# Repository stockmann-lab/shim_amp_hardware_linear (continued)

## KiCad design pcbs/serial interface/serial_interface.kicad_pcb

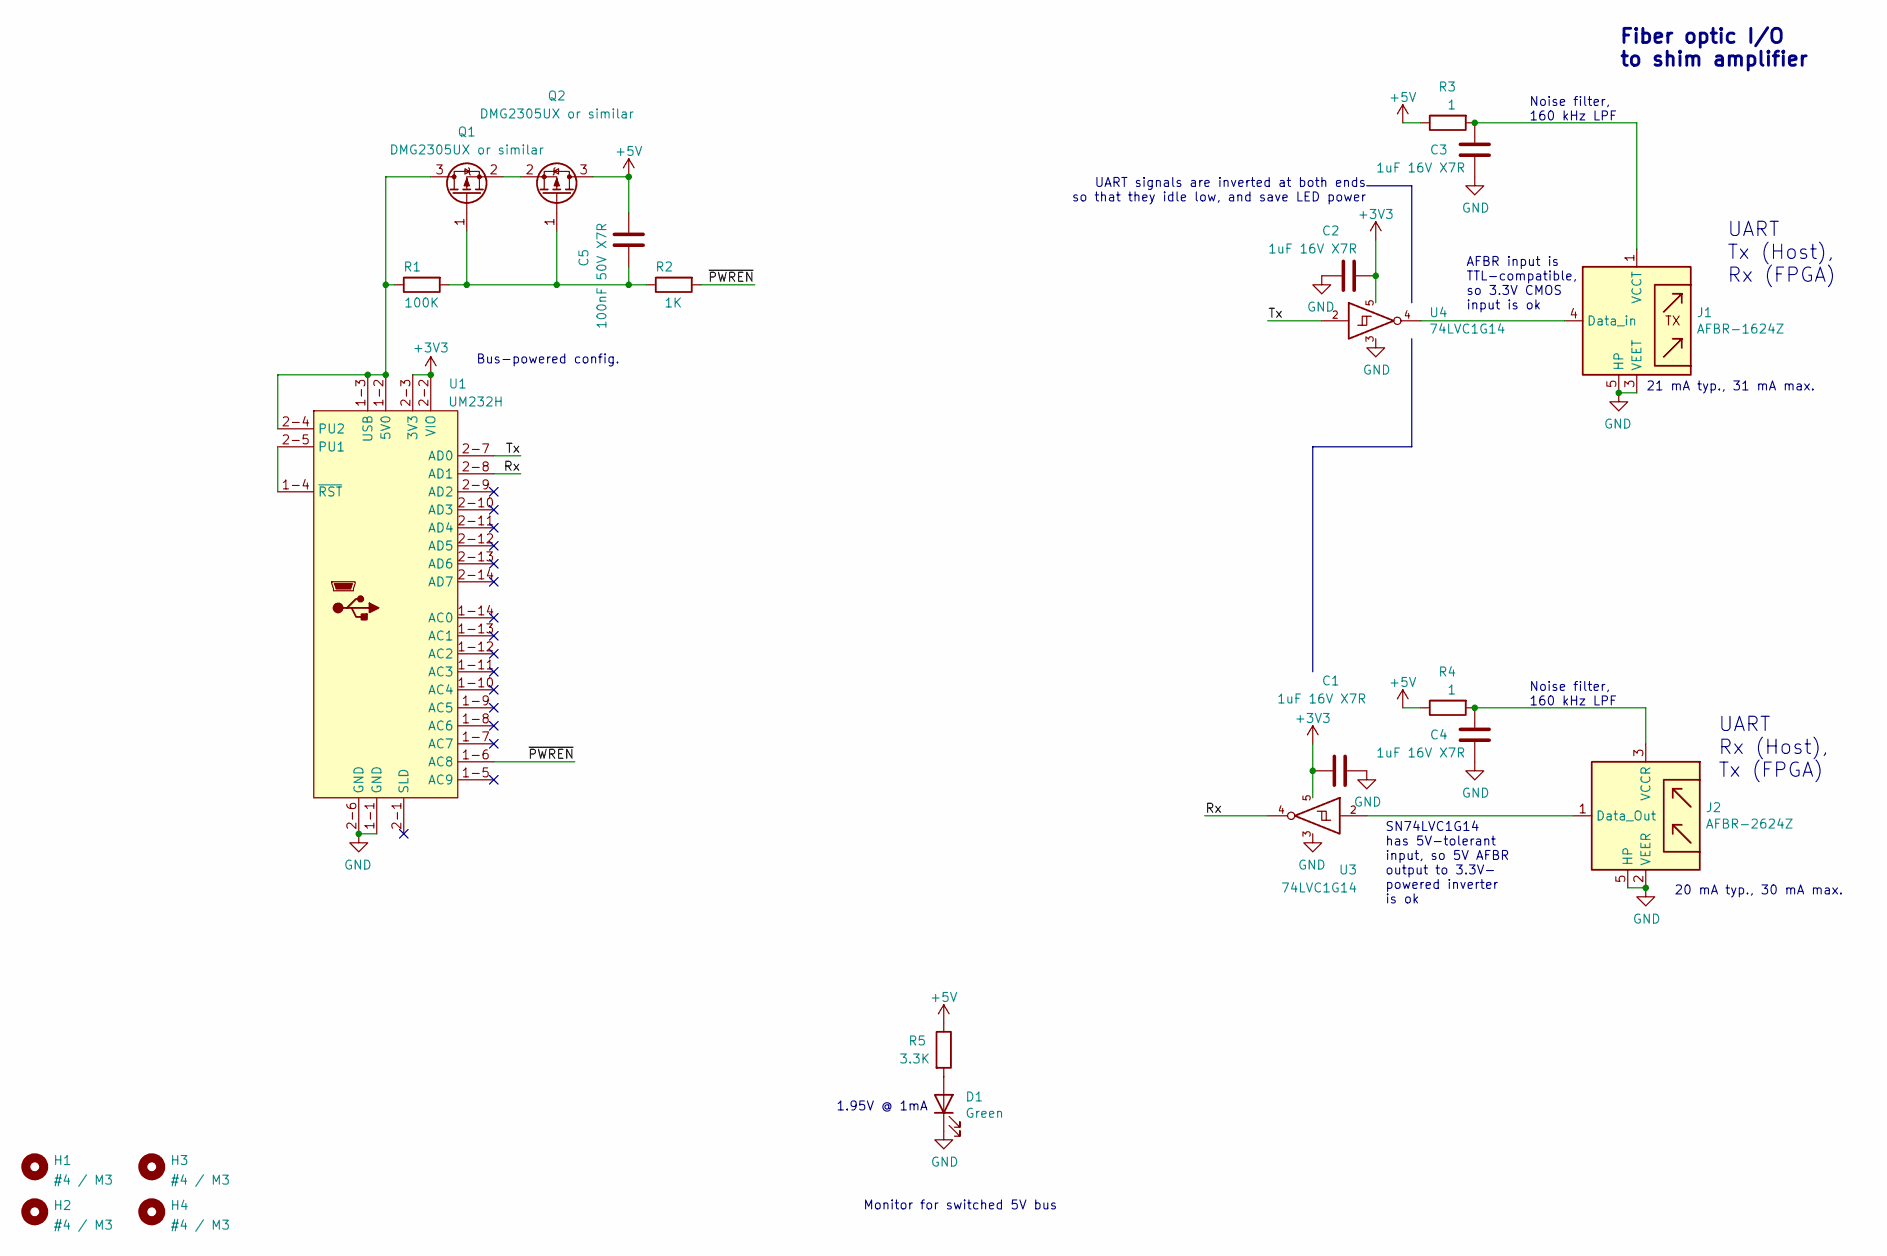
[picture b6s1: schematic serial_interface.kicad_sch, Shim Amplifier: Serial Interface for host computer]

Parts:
C1, C2, C3, C4: 1uF 16V X7R; C_0603_1608Metric; Part Number C0603C105K4RACTU
C5: 100nF 50V X7R; C_0603_1608Metric; Part Number C0603C104K5RAC7867
D1: Green; LED_0805_2012Metric; Part Number LTST-C171KGKT
H1, H2, H3, H4: #4 / M3; MountingHole_3.2mm_M3
J1: AFBR-1624Z; AFBR-xx2xZ; Part Number AFBR-1624Z
J2: AFBR-2624Z; AFBR-xx2xZ; Part Number AFBR-2624Z
Q1, Q2: DMG2305UX or similar; SOT-23
R1: 100K; R_0805_2012Metric
R2: 1K; R_0805_2012Metric
R3, R4: 1; R_0805_2012Metric; Part Number RK73H2ATTD1R00F
R5: 3.3K; R_0805_2012Metric; Part Number RK73H2ATTD1001F
U1: UM232H; FTDI_UM232H; Part Number UM232H
U3, U4: 74LVC1G14; SOT-23-5; Part Number SN74LVC1G14DBVR

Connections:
+3V3: C1.2, C2.2, U1.2-2 (VIO), U1.2-3 (3V3), U3.5 (VCC), U4.5 (VCC)
+5V: C5.2, Q2.3 (D), R3.1, R4.1, R5.1
/Rx: U1.2-8 (AD1), U3.4
/Tx: U1.2-7 (AD0), U4.2
/~PWREN: R2.2, U1.1-6 (AC8)
GND: C1.1, C2.1, C3.1, C4.1, D1.1 (K), J1.3 (VEET), J1.5 (HP), J1.8 (HP), J2.2 (VEER), J2.5 (HP), J2.8 (HP), U1.1-1 (GND), U1.2-6 (GND), U3.3 (GND), U4.3 (GND)
unnamed: D1.2 (A), R5.2
unnamed: J1.4 (Data_in), U4.4
unnamed: C3.2, J1.1 (VCCT), R3.2
unnamed: J2.1 (Data_Out), U3.2
unnamed: C4.2, J2.3 (VCCR), R4.2
unnamed: Q1.3 (D), R1.1, U1.1-2 (5V0), U1.1-3 (USB), U1.2-4 (PU2)
unnamed: C5.1, Q1.1 (G), Q2.1 (G), R1.2, R2.1
unnamed: Q1.2 (S), Q2.2 (S)
unnamed: U1.1-4 (~RST), U1.2-5 (PU1)

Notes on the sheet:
Noise filter, 160 kHz LPF
21 mA typ., 31 mA max.
AFBR input is TTL-compatible, so 3.3V CMOS input is ok
UART Rx (Host), Tx (FPGA)
UART Tx (Host), Rx (FPGA)
UART signals are inverted at both ends so that they idle low, and save LED power
Monitor for switched 5V bus
Bus-powered config.
1.95V @ 1mA
20 mA typ., 30 mA max.
Fiber optic I/O to shim amplifier
SN74LVC1G14 has 5V-tolerant input, so 5V AFBR output to 3.3V- powered inverter is ok

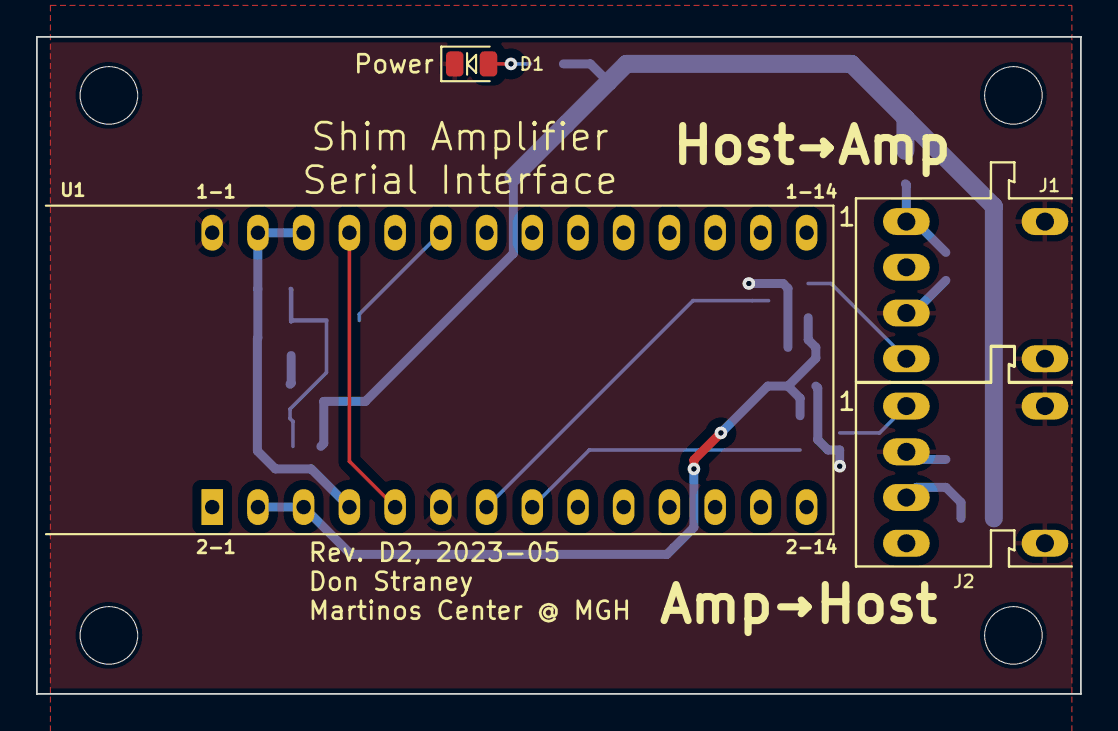
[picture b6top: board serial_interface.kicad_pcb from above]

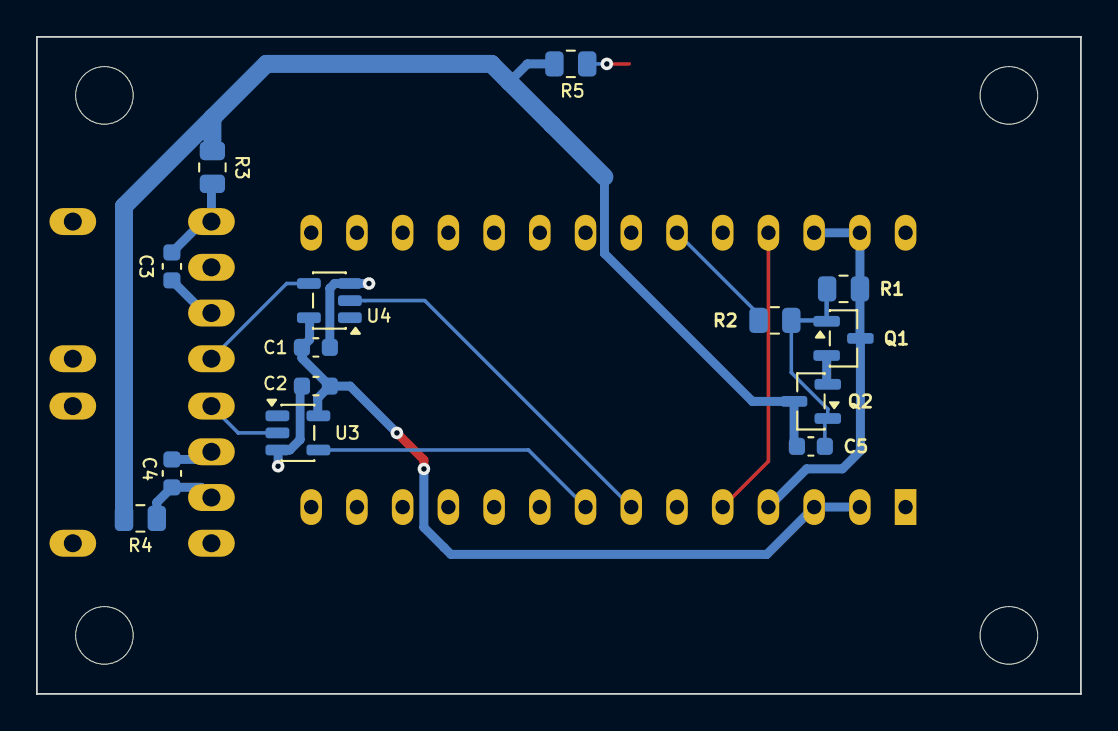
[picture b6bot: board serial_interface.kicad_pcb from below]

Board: 2 copper layers, 58.0 x 36.5 mm, 22 parts (14 on the bottom side), 15 nets.

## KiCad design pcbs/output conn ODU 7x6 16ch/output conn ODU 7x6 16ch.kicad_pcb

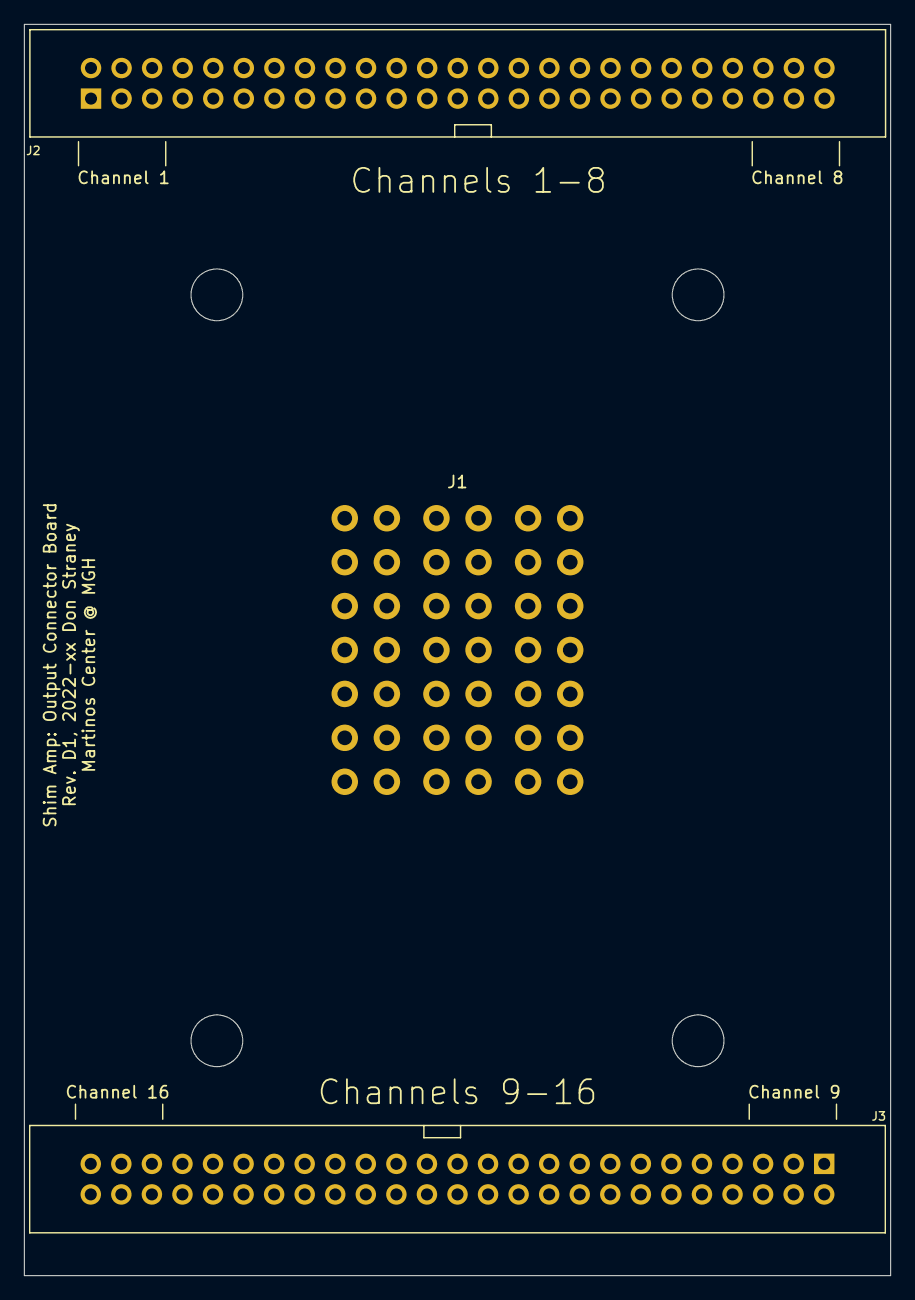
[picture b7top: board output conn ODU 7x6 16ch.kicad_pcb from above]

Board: 4 copper layers, 72.0 x 104.0 mm, 7 parts (1 on the bottom side), 32 nets, no tracks yet.

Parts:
H1, H2, H3, H4: M4; MountingHole_4.3mm_M4
J1: ODU-MAC_Zero_6x7
J2, J3: Conn_02x25_Odd_Even; PinHeader_2x25_P2.54mm_Vertical_Shrouded

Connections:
/P1+: J2.1, J2.3, J2.5
/P1-: J2.2, J2.4, J2.6
/P2+: J2.7, J2.9, J2.11
/P2-: J2.8, J2.10, J2.12
/P3+: J2.13, J2.15, J2.17
/P3-: J2.14, J2.16, J2.18
/P4+: J2.19, J2.21, J2.23
/P4-: J2.20, J2.22, J2.24
/P5+: J2.27, J2.29, J2.31
/P5-: J2.28, J2.30, J2.32
/P6+: J2.33, J2.35, J2.37
/P6-: J2.34, J2.36, J2.38
/P7+: J2.39, J2.41, J2.43
/P7-: J2.40, J2.42, J2.44
/P8+: J2.45, J2.47, J2.49
/P8-: J2.46, J2.48, J2.50
/P9+: J3.1, J3.3, J3.5
/P9-: J3.2, J3.4, J3.6
/P10+: J3.7, J3.9, J3.11
/P10-: J3.8, J3.10, J3.12
/P11+: J3.13, J3.15, J3.17
/P11-: J3.14, J3.16, J3.18
/P12+: J3.19, J3.21, J3.23
/P12-: J3.20, J3.22, J3.24
/P13+: J3.27, J3.29, J3.31
/P13-: J3.28, J3.30, J3.32
/P14+: J3.33, J3.35, J3.37
/P14-: J3.34, J3.36, J3.38
/P15+: J3.39, J3.41, J3.43
/P15-: J3.40, J3.42, J3.44
/P16+: J3.45, J3.47, J3.49
/P16-: J3.46, J3.48, J3.50

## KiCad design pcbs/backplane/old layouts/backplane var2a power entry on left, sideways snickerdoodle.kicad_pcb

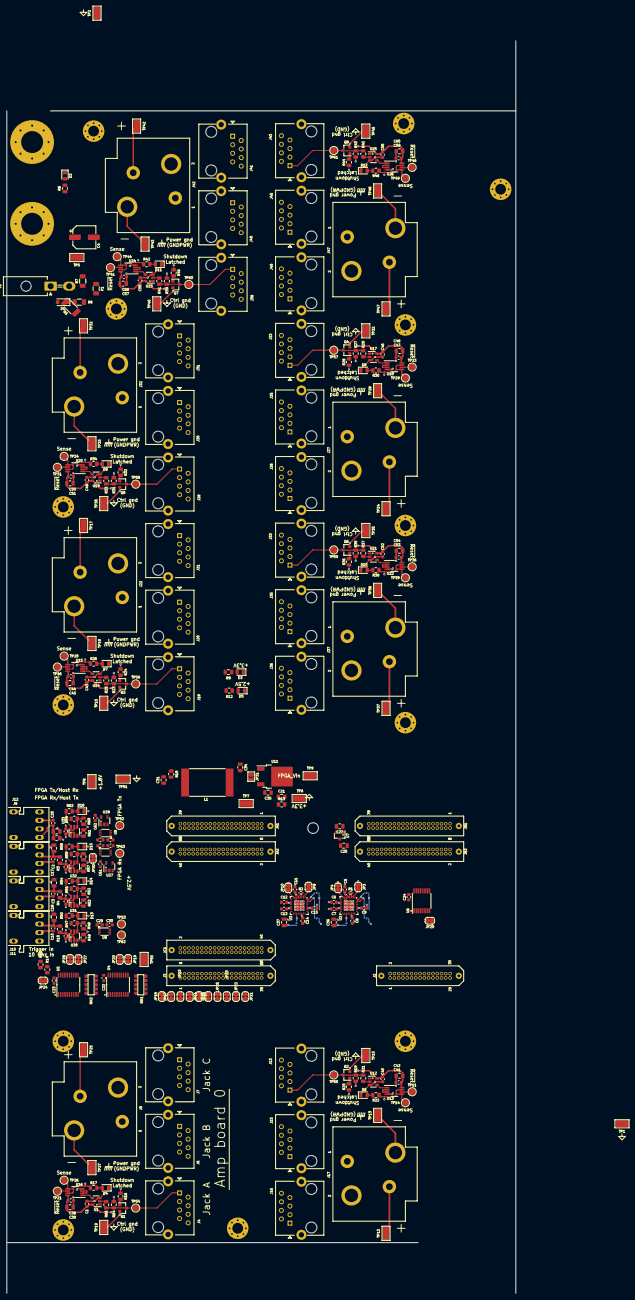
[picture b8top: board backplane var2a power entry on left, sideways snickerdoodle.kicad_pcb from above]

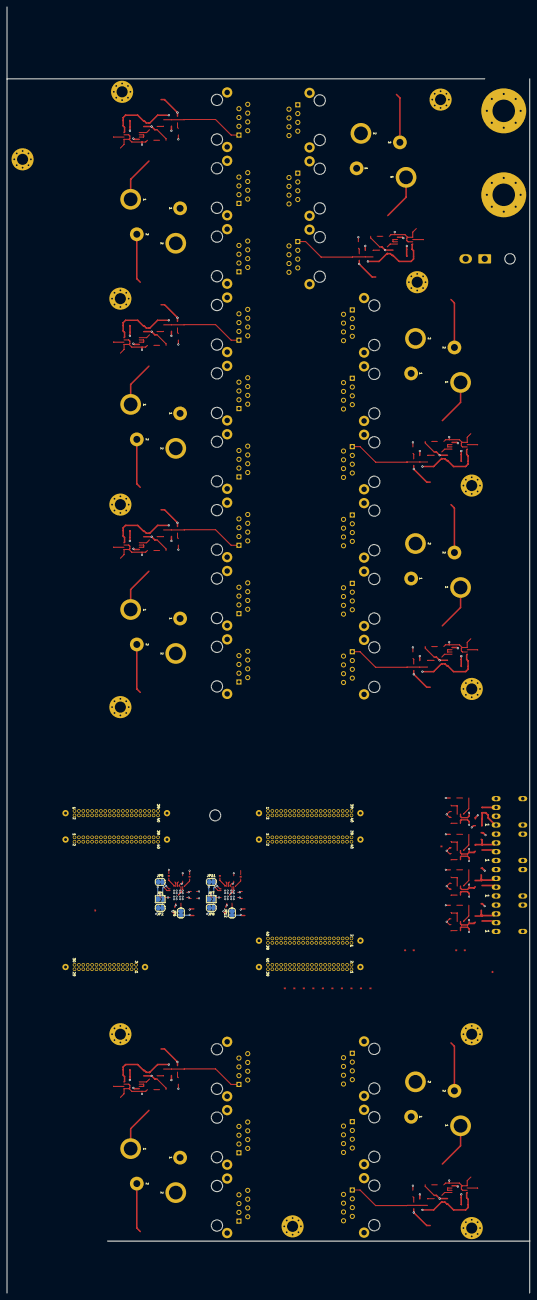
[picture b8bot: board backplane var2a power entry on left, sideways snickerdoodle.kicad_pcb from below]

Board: 6 copper layers, 151.0 x 371.5 mm, 341 parts (8 on the bottom side), 272 nets.

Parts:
C1, C2, C3, C5, C6, C7, C8, C9, C10, C11, C12, C13, C14, C15, C20, C22, C23, C24, C26, C28, C29, C30, C32, C33, C38, C40, C41, C43, C44, C46, C47, C49, C50, C52, C53, C55, C56, C58, C59, C61, C62, C63, C64, C65, C66: 100nF 50V X7R; C_0603_1608Metric
C4: 100uF 35V alum.; CP_Elec_6.3x9.9
C16, C17, C18, C19, C21, C25, C27, C31, C34, C35, C36, C37, C39, C42, C45, C48, C51, C54, C57, C60: 1uF 50V X7R; C_0805_2012Metric
D1: PMEG6010; D_SOD-123F
D2, D3, D5: Green; LED_0805_2012Metric
D4, D6, D7, D8, D9, D10, D11, D12: Red; LED_0805_2012Metric
D13, D14, D15, D16: Yellow; LED_0805_2012Metric
F1: TBD; Fuse_1206_3216Metric
H1, H2: 1/4", M6; MountingHole_6.5mm_Pad_Via
H3, H4, H5, H6, H7, H8, H9, H10, H11, H12, H13, H14, H15: #4/M3; MountingHole_3.2mm_M3_Pad_Via
J1: Conn_01x02; Molex_Mini-Fit_Jr_5569-02A2_2x01_P4.20mm_Horizontal
J2: Conn_02x15_Odd_Even; Conn_Samtec_TFM-115-x1,3-x-D-WT
J3: Conn_02x20_Odd_Even; Conn_Samtec_TFM-120-x1,3-x-D-WT
J4, J6, J7, J13, J15, J16, J18, J20, J21, J23, J25, J26, J28, J30, J31, J33, J35, J36, J38, J40, J41, J43, J45, J46: RJ45_Shielded; RJ45_Amphenol_RJE06-188-1x20
J8, J17, J22, J27, J32, J37, J42, J47: Conn_01x02; Connector_Combo_Molex_386608802_Phoenix_1792229
J9, J10, J11: AFBR-2624Z; AFBR-xx2xZ
J12: AFBR-1624Z; AFBR-xx2xZ
JA1, JA2: Conn_02x20_Odd_Even; Conn_Samtec_TFM-120-x1,3-x-D-WT
JB1, JB2: Conn_02x20_Odd_Even; Conn_Samtec_TFM-120-x1,3-x-D-WT
JC1: Conn_02x20_Odd_Even; Conn_Samtec_TFM-120-x1,3-x-D-WT
JP1, JP7: Jumper_NC_Small; SolderJumper-2_P1.3mm_Open_TrianglePad1.0x1.5mm
JP2, JP3, JP4, JP5, JP6, JP8, JP9, JP10, JP11, JP12, JP13, JP14, JP15, JP17, JP18, JP19, JP20, JP21, JP22, JP23, JP24, JP25, JP26, JP27, JP28, JP29, JP30: Jumper_NC_Small; SolderJumper-2_P1.3mm_Bridged_RoundedPad1.0x1.5mm
JP31: Jumper_NO_Small; SolderJumper-2_P1.3mm_Open_TrianglePad1.0x1.5mm
L1: 500nH; L_Coilcraft_2929SQ-501
Q1, Q2, Q3, Q4, Q5, Q6, Q7, Q8: MMBT3904; SOT-23
R1, R2: 100; R_0402_1005Metric
R3, R4, R10, R11, R13, R18: 1; R_0805_2012Metric
R5: 10 0.25W; R_2010_5025Metric
R6, R7: 1; R_1206_3216Metric
R8: 15K; R_0805_2012Metric
R9, R16, R20, R21, R24, R25, R28, R29, R32, R33, R36, R37, R40, R41, R44, R45, R50, R54, R58, R62, R66: 1K; R_0805_2012Metric
R12: 560; R_0805_2012Metric
R14, R15: 4.7K; R_0805_2012Metric
R17, R22, R26, R30, R34, R38, R42, R46: 3.3K; R_0805_2012Metric
R19, R23, R27, R31, R35, R39, R43, R64: 20K; R_0805_2012Metric
R47, R51, R55, R59: 10K; R_0805_2012Metric
R48, R52, R56, R60: 6.81K; R_0805_2012Metric
R49, R53, R57, R61: 180K; R_0805_2012Metric
RN1, RN2: 4.7K; CTS_745C
TP1, TP2, TP5, TP6, TP7, TP8, TP9, TP10, TP12, TP13, TP15, TP17, TP18, TP19, TP22, TP24, TP25, TP27, TP28, TP30, TP32, TP33, TP35, TP37, TP38, TP40, TP42, TP43, TP45, TP47, TP48, TP50, TP51: TestPoint_Flag; TestPoint_Keystone_5019_Minature
TP11, TP14, TP16, TP20, TP21, TP23, TP26, TP29, TP31, TP34, TP36, TP39, TP41, TP44, TP46, TP49, TP52, TP53, TP54, TP55, TP56, TP57, TP58, TP59, TP60, TP61, TP62, TP63: TestPoint; TestPoint_Pad_D2.0mm
U1, U12, U14, U17, U19, U21, U23, U25: 74LVC1G17; SOT-23-5
U2, U3: CDCUN1208LP; VQFN-32-1EP_5x5mm_P0.5mm_EP3.45x3.45mm
U4, U5: PCA9544APW; TSSOP-20_4.4x6.5mm_P0.65mm
U6: 74HC151; TSSOP-16_4.4x5mm_P0.65mm
U7: AP2120N-2.5; SOT-23
U8, U9, U10: 74LVC2T45; VSSOP-8_2.3x2mm_P0.5mm
U11: 78M15; TO-252-2
U13, U15, U16, U18, U20, U22, U24, U26: 74LVC2G00; VSSOP-8_3.0x3.0mm_P0.65mm
U27, U29: 74LVC1G14; SOT-23-5
U28: Snickerdoodle
U30, U31, U32, U33: LTC6993xS6-2; TSOT-23-6

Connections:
+1.8V: C26.2, C33.2, J3.3, JP24.1, R14.1, R15.1, TP8.1, U8.1, U8.5, U10.8
+2.5V: C1.1, C24.1, C27.2, C30.2, C38.1, C39.2, C40.1, C41.1, C42.2, C43.1, C44.1, C45.2, C46.1, C47.1, C48.2, C49.1, C50.1, C51.2, C52.1, C53.1, C54.2, C55.1, C56.1, C57.2, C58.1, C59.1, C60.2, JA1.3, JA2.3, JB1.3, JB2.3, JC1.3, JP21.1, R12.1, TP7.1, U1.5, U6.16, U7.2, U9.8, U12.5, U13.8, U14.5, U15.8, U16.8, U17.5, U18.8, U19.5, U20.8, U21.5, U22.8, U23.5, U24.8, U25.5, U26.8
+3V3: C5.1, C6.1, C7.1, C8.1, C9.1, C11.1, C12.1, C13.1, C14.1, C15.1, C21.2, C25.2, C28.2, C29.2, C32.2, C36.2, C37.2, C61.2, C62.2, C63.2, C64.2, C65.2, C66.2, JP1.1, JP5.1, JP7.1, JP11.1, JP17.2, JP18.2, JP19.2, JP20.2, JP25.2, JP26.2, JP27.2, JP28.2, R3.1, R4.1, R9.1, R10.1, R11.1, R13.2, R16.1, R20.1, R24.1, R28.1, R32.1, R36.1, R40.1, R44.1, R47.1, R51.1, R55.1, R59.1, RN1.5, RN1.10, RN2.5, RN2.10, TP6.1, U2.5, U2.11, U2.14, U2.22, U2.27, U3.5, U3.11, U3.14, U3.22, U3.27, U7.3, U8.8, U9.1, U9.5, U10.1, U10.5, U27.5, U29.5, U30.5, U31.5, U32.5, U33.5
+VDC: H1.1, J8.2, J17.2, J22.2, J27.2, J32.2, J37.2, J42.2, J47.2, R5.2, R8.1, TP12.1, TP17.1, TP24.1, TP25.1, TP32.1, TP37.1, TP42.1, TP47.1
/ADC_MISO+0: J6.8, JB2.11
/ADC_MISO+1: J15.8, JB1.14
/ADC_MISO+2: J20.8, JC1.14
/ADC_MISO+3: J35.8, JB1.32
/ADC_MISO+4: J30.8, JC1.32
/ADC_MISO+5: J25.8, JA1.14
/ADC_MISO+6: J40.8, JA2.17
/ADC_MISO+7: J45.8, JA2.29
/ADC_MISO-0: J6.7, JB2.13
/ADC_MISO-1: J15.7, JB1.12
/ADC_MISO-2: J20.7, JC1.12
/ADC_MISO-3: J35.7, JB1.30
/ADC_MISO-4: J30.7, JC1.30
/ADC_MISO-5: J25.7, JA1.12
/ADC_MISO-6: J40.7, JA2.19
/ADC_MISO-7: J45.7, JA2.31
/ADC_MOSI+0: J4.4, JB2.8
/ADC_MOSI+1: J13.4, JB1.17
/ADC_MOSI+2: J18.4, JC1.11
/ADC_MOSI+3: J33.4, JB2.32
/ADC_MOSI+4: J28.4, JC1.29
/ADC_MOSI+5: J23.4, JA1.17
/ADC_MOSI+6: J38.4, JA2.14
/ADC_MOSI+7: J43.4, JA1.32
/ADC_MOSI-0: J4.5, JB2.6
/ADC_MOSI-1: J13.5, JB1.19
/ADC_MOSI-2: J18.5, JC1.13
/ADC_MOSI-3: J33.5, JB2.30
/ADC_MOSI-4: J28.5, JC1.31
/ADC_MOSI-5: J23.5, JA1.19
/ADC_MOSI-6: J38.5, JA2.12
/ADC_MOSI-7: J43.5, JA1.30
/Activitiy Indicator (Rx)/In: J9.1, U27.2, U32.1
/Activity Indicator (Trigger)/In: J10.1, U9.2, U31.1
/Activity Indicator (Tx)/In: J12.4, U29.4, U33.1
/Amp board 0 interface/~Shutdown: J4.1, Q1.3, R16.2, R66.2, TP54.1
/Amp board 1 interface/~Shutdown: J13.1, Q2.3, R20.2, R21.2, TP55.1
/Amp board 2 interface/~Shutdown: J18.1, Q3.3, R24.2, R25.2, TP56.1
/Amp board 3 interface/~Shutdown: J33.1, Q6.3, R36.2, R37.2, TP59.1
/Amp board 4 interface/~Shutdown: J28.1, Q5.3, R32.2, R33.2, TP58.1
/Amp board 5 interface/~Shutdown: J23.1, Q4.3, R28.2, R29.2, TP57.1
/Amp board 6 interface/~Shutdown: J38.1, Q7.3, R40.2, R41.2, TP60.1
/Amp board 7 interface/~Shutdown: J43.1, Q8.3, R44.2, R45.2, TP61.1
/DAC_MISO+0: J6.2, JB2.14
/DAC_MISO+1: J15.2, JB1.11
/DAC_MISO+2: J20.2, JC1.17
/DAC_MISO+3: J35.2, JB1.29
/DAC_MISO+4: J30.2, JC1.38
/DAC_MISO+5: J25.2, JA1.11
/DAC_MISO+6: J40.2, JA2.20
/DAC_MISO+7: J45.2, JA2.32
/DAC_MISO-0: J6.1, JB2.12
/DAC_MISO-1: J15.1, JB1.13
/DAC_MISO-2: J20.1, JC1.19
/DAC_MISO-3: J35.1, JB1.31
/DAC_MISO-4: J30.1, JC1.36
/DAC_MISO-5: J25.1, JA1.13
/DAC_MISO-6: J40.1, JA2.18
/DAC_MISO-7: J45.1, JA2.30
/DAC_MOSI+0: J7.5, JB2.20
/DAC_MOSI+1: J16.5, JB1.5
/DAC_MOSI+2: J21.5, JC1.23
/DAC_MOSI+3: J36.5, JB1.23
/DAC_MOSI+4: J31.5, JA2.8
/DAC_MOSI+5: J26.5, JA1.5
/DAC_MOSI+6: J41.5, JA2.26
/DAC_MOSI+7: J46.5, JA1.26
/DAC_MOSI-0: J7.4, JB2.18
/DAC_MOSI-1: J16.4, JB1.7
/DAC_MOSI-2: J21.4, JC1.25
/DAC_MOSI-3: J36.4, JB1.25
/DAC_MOSI-4: J31.4, JA2.6
/DAC_MOSI-5: J26.4, JA1.7
/DAC_MOSI-6: J41.4, JA2.24
/DAC_MOSI-7: J46.4, JA1.24
/FPGA Board, Signal Distribution/10Mhz: J11.1, U9.3, U30.1
/FPGA Board, Signal Distribution/10Mhz_2.5: JB2.38, TP62.1, U9.6
/FPGA Board, Signal Distribution/FPGA_Vin: C35.2, J2.29, J2.30, JP31.2, TP9.1, U11.3
/FPGA Board, Signal Distribution/SCKI+: JB2.26, R1.2, U2.3
/FPGA Board, Signal Distribution/SCKI-: JB2.24, R1.1, U2.4
/FPGA Board, Signal Distribution/SCL: J3.38, R15.2, U4.18, U5.18
/FPGA Board, Signal Distribution/SDA: J3.36, R14.2, U4.19, U5.19
/FPGA Board, Signal Distribution/Shutdown_Sense: JA2.4, U6.5
/FPGA Board, Signal Distribution/Shutdown_Sense_Sel0: JB2.4, U6.11
/FPGA Board, Signal Distribution/Shutdown_Sense_Sel1: JB1.4, U6.10
/FPGA Board, Signal Distribution/Shutdown_Sense_Sel2: JC1.4, U6.9
/FPGA Board, Signal Distribution/Trigger_2.5: JB2.36, TP53.1, U9.7
/FPGA Board, Signal Distribution/UART_Rx_FPGA: U10.2, U27.4
/FPGA Board, Signal Distribution/UART_Rx_FPGA_1.8: J3.37, TP63.1, U10.7
/FPGA Board, Signal Distribution/UART_Tx_FPGA: U8.6, U29.2
/FPGA Board, Signal Distribution/UART_Tx_FPGA_1.8: J3.35, TP52.1, U8.3
/FPGA Board, Signal Distribution/~FPGA_Rst_1.8: J2.19, U8.2
/FPGA Board, Signal Distribution/~LDAC+: JB2.23, R2.2, U3.3
/FPGA Board, Signal Distribution/~LDAC-: JB2.25, R2.1, U3.4
/SCKI+0: J7.2, U2.10
/SCKI+1: J16.2, U2.13
/SCKI+2: J21.2, U2.16
/SCKI+3: J36.2, U2.18
/SCKI+4: J31.2, U2.21
/SCKI+5: J26.2, U2.24
/SCKI+6: J41.2, U2.26
/SCKI+7: J46.2, U2.29
/SCKI-0: J7.1, U2.9
/SCKI-1: J16.1, U2.12
/SCKI-2: J21.1, U2.15
/SCKI-3: J36.1, U2.17
/SCKI-4: J31.1, U2.20
/SCKI-5: J26.1, U2.23
/SCKI-6: J41.1, U2.25
/SCKI-7: J46.1, U2.28
/SCKO+0: J6.5, JB2.35
/SCKO+1: J15.5, JB1.38
/SCKO+2: J20.5, JC1.8
/SCKO+3: J35.5, JB1.35
/SCKO+4: J30.5, JC1.35
/SCKO+5: J25.5, JA1.38
/SCKO+6: J40.5, JA2.38
/SCKO+7: J45.5, JA2.35
/SCKO-0: J6.4, JB2.37
/SCKO-1: J15.4, JB1.36
/SCKO-2: J20.4, JC1.6
/SCKO-3: J35.4, JB1.37
/SCKO-4: J30.4, JC1.37
/SCKO-5: J25.4, JA1.36
/SCKO-6: J40.4, JA2.36
/SCKO-7: J45.4, JA2.37
/SCL0: J4.3, RN1.2, U4.6
/SCL1: J13.3, RN1.4, U4.9
/SCL2: J18.3, RN1.8, U4.13
/SCL3: J33.3, RN1.6, U4.16
/SCL4: J28.3, RN2.2, U5.6
/SCL5: J23.3, RN2.4, U5.9
/SCL6: J38.3, RN2.8, U5.13
/SCL7: J43.3, RN2.6, U5.16
/SDA0: J4.6, RN1.1, U4.5
/SDA1: J13.6, RN1.3, U4.8
/SDA2: J18.6, RN1.9, U4.12
/SDA3: J33.6, RN1.7, U4.15
/SDA4: J28.6, RN2.1, U5.5
/SDA5: J23.6, RN2.3, U5.8
/SDA6: J38.6, RN2.9, U5.12
/SDA7: J43.6, RN2.7, U5.15
/Shutdown_Force: JA1.23, R19.2, R23.2, R27.2, R31.2, R35.2, R39.2, R43.2, R64.2
/Shutdown_Sense0: R17.2, TP26.1, U6.4, U16.5, U16.7
/Shutdown_Sense1: R22.2, TP14.1, U6.3, U13.5, U13.7
/Shutdown_Sense2: R26.2, TP20.1, U6.2, U15.5, U15.7
/Shutdown_Sense3: R38.2, TP39.1, U6.1, U22.5, U22.7
/Shutdown_Sense4: R34.2, TP34.1, U6.15, U20.5, U20.7
/Shutdown_Sense5: R30.2, TP29.1, U6.14, U18.5, U18.7
/Shutdown_Sense6: R42.2, TP44.1, U6.13, U24.5, U24.7
/Shutdown_Sense7: R46.2, TP49.1, U6.12, U26.5, U26.7
/~ADC_CS+0: J4.7, JB2.5
/~ADC_CS+1: J13.7, JB1.20
/~ADC_CS+2: J18.7, JC1.5
/~ADC_CS+3: J33.7, JB2.29
/~ADC_CS+4: J28.7, JC1.26
/~ADC_CS+5: J23.7, JA1.20
/~ADC_CS+6: J38.7, JA2.11
/~ADC_CS+7: J43.7, JA1.35
/~ADC_CS-0: J4.8, JB2.7
/~ADC_CS-1: J13.8, JB1.18
/~ADC_CS-2: J18.8, JC1.7
/~ADC_CS-3: J33.8, JB2.31
/~ADC_CS-4: J28.8, JC1.24
/~ADC_CS-5: J23.8, JA1.18
/~ADC_CS-6: J38.8, JA2.13
/~ADC_CS-7: J43.8, JA1.37
/~Shutdown_Reset: JA1.4, TP11.1, TP16.1, TP21.1, TP23.1, TP31.1, TP36.1, TP41.1, TP46.1, U13.6, U15.6, U16.6, U18.6, U20.6, U22.6, U24.6, U26.6
GND: C1.2, C2.2, C3.2, C4.2, C5.2, C6.2, C7.2, C8.2, C9.2, C10.2, C11.2, C12.2, C13.2, C14.2, C15.2, C16.1, C17.1, C18.1, C19.1, C20.2, C21.1, C22.2, C23.2, C24.2, C25.1, C26.1, C27.1, C28.1, C29.1, C30.1, C31.1, C32.1, C33.1, C34.1, C35.1, C36.1, C37.1, C38.2, C39.1, C40.2, C41.2, C42.1, C43.2, C44.2, C45.1, C46.2, C47.2, C48.1, C49.2, C50.2, C51.1, C52.2, C53.2, C54.1, C55.2, C56.2, C57.1, C58.2, C59.2, C60.1, C61.1, C62.1, C63.1, C64.1, C65.1, C66.1, D2.1, D3.1, D4.1, D5.1, D6.1, D7.1, D8.1, D9.1, D10.1, D11.1, D12.1, D13.1, D14.1, D15.1, D16.1, H4.1, H5.1, H7.1, H8.1, H9.1, H10.1, H11.1, H12.1, H13.1, H14.1, H15.1, J2.5, J2.6, J2.9, J2.10, J2.20, J2.26, J2.27, J2.28, J3.9, J3.10, J3.15, J3.16, J3.21, J3.22, J3.27, J3.28, J3.33, J3.34, J4.2, J4.SH, J6.SH, J7.SH, J9.2, J9.5, J10.2, J10.5, J11.2, J11.5, J12.3, J12.5, J13.2, J13.SH, J15.SH, J16.SH, J18.2, J18.SH, J20.SH, J21.SH, J23.2, J23.SH, J25.SH, J26.SH, J28.2, J28.SH, J30.SH, J31.SH, J33.2, J33.SH, J35.SH, J36.SH, J38.2, J38.SH, J40.SH, J41.SH, J43.2, J43.SH, J45.SH, J46.SH, JA1.9, JA1.10, JA1.15, JA1.16, JA1.21, JA1.22, JA1.27, JA1.28, JA1.33, JA1.34, JA2.9, JA2.10, JA2.15, JA2.16, JA2.21, JA2.22, JA2.27, JA2.28, JA2.33, JA2.34, JB1.9, JB1.10, JB1.15, JB1.16, JB1.21, JB1.22, JB1.27, JB1.28, JB1.33, JB1.34, JB2.9, JB2.10, JB2.15, JB2.16, JB2.21, JB2.22, JB2.27, JB2.28, JB2.33, JB2.34, JC1.9, JC1.10, JC1.15, JC1.16, JC1.21, JC1.22, JC1.27, JC1.28, JC1.33, JC1.34, JP2.2, JP3.1, JP4.1, JP6.1, JP8.2, JP9.1, JP10.1, JP12.1, JP13.1, JP14.1, JP15.1, JP22.1, JP23.1, JP29.1, JP30.1, Q1.2, Q2.2, Q3.2, Q4.2, Q5.2, Q6.2, Q7.2, Q8.2, R7.1, R48.2, R49.2, R52.2, R53.2, R56.2, R57.2, R60.2, R61.2, TP1.1, TP2.1, TP10.1, TP15.1, TP19.1, TP22.1, TP30.1, TP35.1, TP40.1, TP45.1, TP50.1, TP51.1, U1.3, U2.6, U2.7, U2.33, U3.6, U3.7, U3.33, U4.10, U5.10, U6.8, U7.1, U8.4, U9.4, U10.4, U11.2, U12.3, U13.4, U14.3, U15.4, U16.4, U17.3, U18.4, U19.3, U20.4, U21.3, U22.4, U23.3, U24.4, U25.3, U26.4, U27.3, U29.3, U30.2, U31.2, U32.2, U33.2
GNDPWR: H2.1, H3.1, H6.1, J8.1, J17.1, J22.1, J27.1, J32.1, J37.1, J42.1, J47.1, TP13.1, TP18.1, TP27.1, TP28.1, TP33.1, TP38.1, TP43.1, TP48.1
unnamed: C10.1, C18.2, J11.3, R10.2
unnamed: C2.1, C16.2, J9.3, R3.2
unnamed: C3.1, C17.2, J10.3, R4.2
unnamed: C19.2, C20.1, J12.1, R11.2
unnamed: C22.1, C23.1, JP24.2, U4.20, U5.20
unnamed: C34.2, JP31.1, L1.2, U11.1
unnamed: D1.1, R6.2
unnamed: D1.2, J1.1
unnamed: D2.2, R8.2
unnamed: D3.2, R9.2
unnamed: D4.2, R17.1
unnamed: D5.2, R12.2
unnamed: D6.2, R22.1
unnamed: D7.2, R26.1
unnamed: D8.2, R30.1
unnamed: D9.2, R34.1
unnamed: D10.2, R38.1
unnamed: D11.2, R42.1
unnamed: D12.2, R46.1
unnamed: D13.2, R50.2
unnamed: D14.2, R54.2
unnamed: D15.2, R58.2
unnamed: D16.2, R62.2
unnamed: F1.2, R5.1, R6.1
unnamed: J1.2, R7.2
unnamed: JA1.1, R13.1
unnamed: JP1.2, JP2.1, U2.31
unnamed: JP3.2, U2.2
unnamed: JP4.2, U2.8
unnamed: JP5.2, U2.32
unnamed: JP6.2, U2.19
unnamed: JP7.2, JP8.1, U3.31
unnamed: JP9.2, U3.2
unnamed: JP10.2, U3.8
unnamed: JP11.2, U3.32
unnamed: JP12.2, U3.19
unnamed: JP13.2, U4.1
unnamed: JP14.2, U4.2
unnamed: JP15.2, U4.3
unnamed: JP17.1, U4.4
unnamed: JP18.1, U4.7
unnamed: JP19.1, U4.11
unnamed: JP20.1, U4.14
unnamed: JP21.2, U5.1
unnamed: JP22.2, U5.2
unnamed: JP23.2, U5.3
unnamed: JP25.1, U5.4
unnamed: JP26.1, U5.7
unnamed: JP27.1, U5.11
unnamed: JP28.1, U5.14
unnamed: JP29.2, U6.7
unnamed: JP30.2, U10.3
unnamed: L1.1, R18.1
unnamed: Q1.1, R64.1
unnamed: Q2.1, R19.1
unnamed: Q3.1, R23.1
unnamed: Q4.1, R27.1
unnamed: Q5.1, R31.1
unnamed: Q6.1, R35.1
unnamed: Q7.1, R39.1
unnamed: Q8.1, R43.1
unnamed: R21.1, U12.2
unnamed: R25.1, U14.2
unnamed: R29.1, U17.2
unnamed: R33.1, U19.2
unnamed: R37.1, U21.2
unnamed: R41.1, U23.2
unnamed: R45.1, U25.2
unnamed: R47.2, R48.1, U30.4
unnamed: R49.1, U30.3
unnamed: R50.1, U30.6
unnamed: R51.2, R52.1, U31.4
unnamed: R53.1, U31.3
unnamed: R54.1, U31.6
unnamed: R55.2, R56.1, U32.4
unnamed: R57.1, U32.3
unnamed: R58.1, U32.6
unnamed: R59.2, R60.1, U33.4
unnamed: R61.1, U33.3
unnamed: R62.1, U33.6
unnamed: R66.1, U1.2
unnamed: U1.4, U16.1
unnamed: U12.4, U13.1
unnamed: U13.2, U13.3
unnamed: U14.4, U15.1
unnamed: U15.2, U15.3
unnamed: U16.2, U16.3
unnamed: U17.4, U18.1
unnamed: U18.2, U18.3
unnamed: U19.4, U20.1
unnamed: U20.2, U20.3
unnamed: U21.4, U22.1
unnamed: U22.2, U22.3
unnamed: U23.4, U24.1
unnamed: U24.2, U24.3
unnamed: U25.4, U26.1
unnamed: U26.2, U26.3
VD: C4.1, C31.2, F1.1, R18.2, TP5.1

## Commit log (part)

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2023-01-12 initial_commit
2023-01-23 Initial commit of in-progress work from Dropbox shared folder
2023-01-23 Removed extra files Deleted logs, backups, etc. created by KiCAD which shouldn't be in repo Added proper gitignore to keep these from coming back
2023-01-23 Started 7x6 16-channel connector board Adapted schem from 10x9 32-channel connector board Partial layout update, channel assignment silkscreen & routing TBD
2023-01-28 Migrated PCB designs to KiCAD 6
2023-01-31 Minor PCB/project edits
2023-01-31 Schematic file fix, misc. PCB
    Fixed issue with KiCAD's automatic V5→V6 migration (corrected in 6.0.11) that caused problems with component references in multi-channel schematic sheets
    Finished migration in amp ctrl PCB, inc. re-assigning "exclude from BOM" attributes to testpoints, solder jumpers
    Added mounting hole to amp ctrl PCB for addl support to Ethernet jacks, power connector through stiffener
2023-02-04 Added stiffener outline to amp ctrl PCB on new layer
2023-02-06 Stiffener, positioning adjustments
    Moved offset-cal zeners+series resistor out of the way on channels 4 and 8 to avoid mounting holes
    Added holes to stiffener layer
    Moved main fuse to correct excessively-thin stiffener near power input connector
    Adjusted vertical sections of stiffener to take full advantage of space, avoid excessively-thin areas around pass-through holes
2023-02-14 Ctrl board stiffener, ODU connector board
    Finished ctrl board stiffener, re-arranged output connector jumpers to fit cleanly without overlapping stiffener
    Re-named ODU 7x6 connector board for future "backwards direction pin-assignment" version, first-pass layout, added EMI caps
2023-05-03 Removed local settings files, cached libraries from 5.x no longer req'd by 6.x
2023-05-03 New CS amp, misc. layout
    Changed current sense amp from INA828 to INA821/819 due to availability: schematic, layout for channel 1 (#6)
    Moved some thermistor components & ~Shutdown cap out of the way of the stiffener (#3)
    Updated footprints: SOD-323F for slightly larger solderable pads, SOIC-8 to remove excessive length on inside edge
2023-05-03 Channel replication, layout wrap-up
    Copied amp control board channel 1 layout to all channels (#3)
    Amp control board inter-channel routing (#3)
    Silkscreen re-arrangement on amp control board
2023-05-03 New DAC
    Changed DAC from LTC2656 to AD5676 (#5)
    Changed digital Vdd for ADC to +3.3V
    Removed level translator ICs for +3.3V to +5V; no longer needed because AD5676 has separate analog and digital supply pins
2023-05-04 DRC fixes
    Deleted track stubs and overlapping vias, other misc. DRC fixes (#3)
    Shrank width of SOT-563 pads to fall within 0.16 mm clearance (6.3 mils)
2023-05-04 Manufacturing fixes for amp control board
    Arranged *.Fab text for assembly drawings
    Minor stiffener outline fixes, silkscreen fixes
    Fixed missing BOM fields on some parts
    Removed exported manufacturing files from version control
2023-05-17 Corrected amp board ADC op-amp, created ODU connector 6x7 board
    Pared down list of ADC driver op-amps to list of ones tested
    Minor fixes to ODU 6x7 connector board (forward-pinned)
    Created duplicate of ODU 6x7 connector board, for reverse-pinned
2023-05-17 Serial interface speed improvement
    Upgraded serial interface to KiCAD 7.0
    Replaced USB-serial modules with higher-speed (12 Mbps) one (#7)
2023-08-22 Misc. mfg
    Marked top-side testpoints on amp control board as DNP
    Updated serial interface board's BOM-placement-help file
    Exported stiffener file for amp control board
2024-01-12 Upgraded to KiCAD 7.0 format Added 10µF cap to ADC's REFP pins to fix the voltage reference output (#15) Corrected ADC & DAC reset by adding a separate reset circuit (#14) Increased Cfbk compensation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
2024-11-11 Amp ctrl: lengthened ADC & DAC reset delay to ~50 ms (#14) Backplane: added clock multiplier for 10 Mhz scanner clock (fixes #21) Backplane: reduced R5 from 10 to 1 ohm, to avoid excessive voltage dr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
2025-02-08 Comms fix, misc. improvements
    Added 33KΩ pull-ups & pull-downs to amp ctrl board's LVDS inputs, to solve issues caused by unconfigured FPGA pins during boot (fixes #23)
    Swapped backplane power input polarity for consistency with power connectors (fixes #20)
    Added "manual enable" optical input to backplane, for safety: requires positive enable to keep amplifiers enabled
2025-04-27 Corrected power-up behavior
    Backplane: Inverted polarity of Shutdown_Force (now Power_Enable_FPGA), to keep amps powered off until software starts: fixes #23
    Backplane: Routed Shutdown_Force to unused pin 3 on RJ45 jack B to amp boards: fixes #23
    Backplane: Added pull-up and pull-down resistors to fanout buffer inputs, to keep SCK & ~LDAC signals in proper state during power-on: fixes #23
    Amp control: Added transistor to reset DAC & ADC from pin 3 of RJ45 jack B
2025-04-30 Misc. cleanup for mfg & improvements
    Minor backplane pinout doc corrections (SCKO5 polarity, clarified some descriptions)
    Backplane: Added differential- and common-mode (to standoffs) power filtering, for EMI escaping over power wiring
    Amp ctrl: Changed DAC testpoints from individual pads to Keystone 5019 for easier probing
    Corrected part numbers, DNP vs. non-BOM-item indications, other misc. BOM issues
2025-05-02 Backplane cleanup for mfg, schematic clarifications, added alt. power connectors
2025-07-19 Updated KiCAD file versions to 9.0
2025-07-19 Moved all project-specific symbols & footprints into new "shim" libraries Updated projects to reference the new "shim" library
2025-07-19 Finished migrating footprint names
2025-07-19 Updated library references to 3D models, added 3D model directory & appropriate gitignore to omit proprietary models
2025-07-30 Added extra channels to fwd and bck boards
2025-07-30 Added ODU footprints
2025-08-06 Minor tweaks to pathing for the amp_ctrl board to add clearance to screws
2025-08-15 Added initial user guide to docs
2025-08-20 Danny Changes 2025 - Rev D2 of output connector board
2025-08-20 Added gitignore to ignore lock files
2025-08-26 Functional fixes for ADC clk, +3.3V sag on backplane
    Amp ctrl: Added ADC clock inversion (fixes #34)
    Backplane: fixed series-resistor-induced voltage sag (fixes #33)
2025-10-16 BOM & reset fixes
    Amp ctrl: changed name of "Manufacturer" field to "MPN" to work with Aisler
    Amp ctrl: added part number to logic inverter, corrected various typos and part number problems
    Backplane: added pull-down to Shutdown_Reset signal (#35)
    Backplane: rethought Shutdown_Force circuit to make fail-safe (broken connections->shutdown), make work correctly (fixes #35)
    Backplane: updated/corrected various schematic annotations
2025-11-17 Added first draft of the optical control board (UART not included)
2025-11-17 Added some silkscreen to the fiber control board
2025-11-19 Tweaked serial interface and fiber control boards. Added empty manufacturing folder to indicate where to dump gerbers
2025-11-19 More small tweaks
2026-06-22 Added rev_d_shim and zynq_toolbox repo references in README
2026-06-22 Add DOI badge to README
    Added a DOI badge for citation in the README.
